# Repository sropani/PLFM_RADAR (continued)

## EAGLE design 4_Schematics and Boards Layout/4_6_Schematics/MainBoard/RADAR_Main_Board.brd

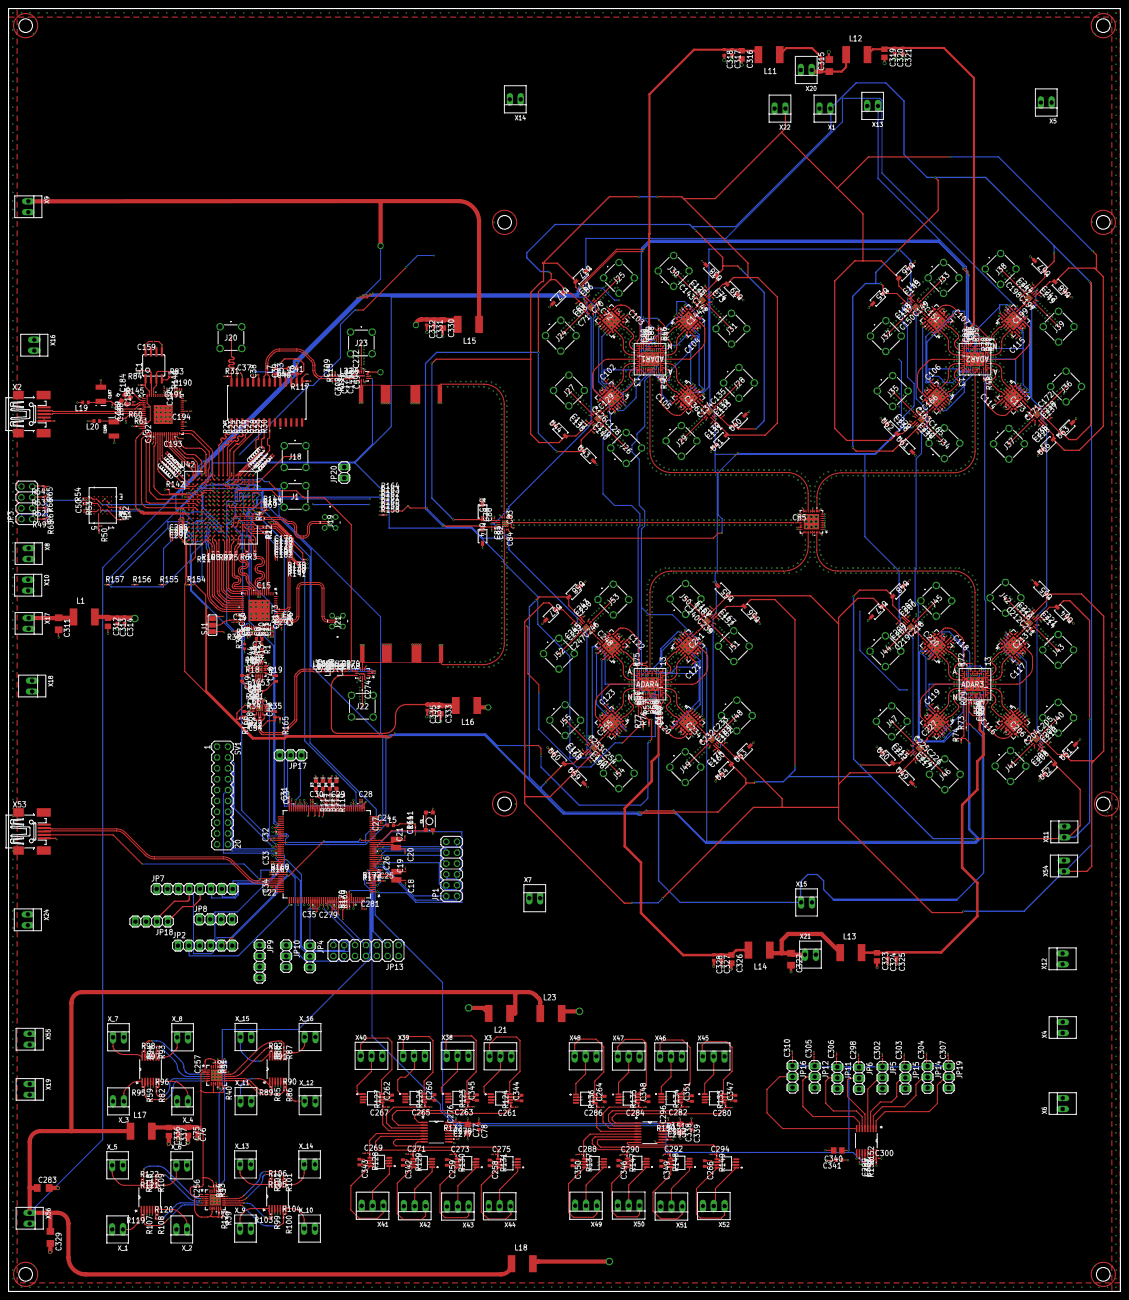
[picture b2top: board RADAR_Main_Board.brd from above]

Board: 10 copper layers, 260.0 x 300.0 mm, 789 parts (0 on the bottom side), 649 nets.

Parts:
ADAR1_, ADAR2_, ADAR3_, ADAR4_: ADAR1000ACCZN; CC-88-1_ADI
ADTR1107_1, ADTR1107_2, ADTR1107_3, ADTR1107_4, ADTR1107_5, ADTR1107_6, ADTR1107_7, ADTR1107_8, ADTR1107_9, ADTR1107_10, ADTR1107_11, ADTR1107_12, ADTR1107_13, ADTR1107_14, ADTR1107_15, ADTR1107_16: ADTR1107ACCZ; CC-24-8_ADI
C1, C2, C4, C5, C6, C7, C8, C9, C10, C11, C12, C13, C14, C15, C16, C36, C38, C39, C41, C42, C44, C45, C46, C47, C51, C52, C53, C56, C67, C69, C74, C80, C82, C125, C131, C133, C138, C140, C146, C148, C159, C160, C162, C168, C170, C175, C188, C189, C190, C192, C193, C194, C195, C196, C201, C203, C208, C210, C215, C217, C222, C224, C229, C231, C236, C238, C243, C245, C250, C252, C293: 0.1uF; C0201
C3: 2.7pF; C0402
C17, C55, C176, C285: 47uF; C0201
C18, C19: 2.7pF; C0201
C20, C21: 4.3pF; C0201
C22, C23, C164: 2.2uF; C0201
C24, C25, C26, C27, C28, C29, C30, C32, C33, C34, C35, C50, C256, C257, C279, C281, C298, C302, C303, C304, C305, C306, C307, C310: 100nF; C0201
C31: 47nF; C0201
C37, C40: 10uF; C0201
C43: 0.2pF; C0201
C48, C49, C57, C58: 0.1µF; C0402
C54: 0.6pF; C0201
C59, C127: 32.8pF; C0201
C60, C63: 103pF; C0201
C61, C62: 7.8pF; C0201
C64, C65, C268, C270: 25pF; C0201
C66, C68, C73, C79, C81, C124, C130, C132, C137, C139, C145, C147, C152, C161, C167, C169, C174, C183, C200, C202, C207, C209, C214, C216, C221, C223, C228, C230, C235, C237, C242, C244, C249, C251: 100pF; C0201
C70, C71, C72, C83, C84, C85, C126, C128, C129, C134, C135, C136, C142, C143, C144, C149, C150, C151, C163, C165, C166, C171, C172, C173, C197, C198, C199, C204, C205, C206, C211, C212, C213, C218, C219, C220, C225, C226, C227, C232, C233, C234, C239, C240, C241, C246, C247, C248, C253, C254, C255: 1pF; C0201
C75, C77, C312, C316, C319, C323, C326, C330, C333, C336, C338, C340: 10µF; C0805
C76, C78, C258, C259, C260, C262, C264, C266, C313, C317, C320, C324, C327, C331, C334, C337, C339, C341, C342, C343, C344, C345, C346, C347, C348, C349, C350, C351: 100nF; C0402
C86, C87, C88, C89, C90, C91, C92, C93, C94, C95, C96, C97, C98, C99, C100, C101: 1uF; C0201
C102, C103, C104, C105, C106, C107, C114, C115, C116, C117, C118, C119, C120, C121, C122, C123: 10nF; C0201
C108, C109, C153, C154, C177, C178, C287, C289: 4.7uF; C0201
C110, C111, C112, C113, C155, C156, C157, C158, C179, C180, C181, C182, C291: 0.47uF; C0201
C141: 106pF; C0201
C184, C185: 12pF; C0201
C186, C187: 4.7uF 35V; EIA3528
C191: 3.3uF; C0201
C261, C263, C265, C267, C269, C271, C273, C275, C280, C282, C284, C286, C288, C290, C292, C294: 4.7nF; C0201
C272, C274: 18pF; C0201
C276, C296, C300: 1µF; C0201
C277, C278, C295, C297, C299, C301: 0.1µF; C0201
C283, C311, C315, C322, C329: 22µF; C1206
C308, C309: 22pF; C0201
C314, C318, C321, C325, C328, C332, C335: 1nF; C0402
D2, D3, D4, D5: Blue; LED-0603
IC1: AT93C46A-10SQ-2.7; SOIC8
J1, J18, J20, J22, J23, J24, J25, J26, J27, J28, J29, J30, J31, J32, J33, J34, J35, J36, J37, J38, J39, J40, J41, J42, J43, J44, J45, J46, J47, J48, J49, J50, J51, J52, J53, J54, J55: 142-0731-211; 1420731211
J19, J21: CJT-T-P-HH-ST-TH1; CJTTPHHSTTH1
JP1: 2X06
JP2: 1X06
JP3: 2X04
JP4, JP5, JP6, JP10, JP11, JP12, JP14, JP15, JP16, JP17, JP19: 1X03
JP7: 1X08
JP8, JP9, JP18: 1X04
JP13: 2X07
JP20: 1X02
L1, L11, L12, L13, L14, L15, L16, L17, L18, L21, L23: L5650M
L2, L8: 12nH; L0201
L3, L4: 159nH; L0201
L5, L6, L7, L19, L20: BLM15HB121SN1; 0402
L9, L10, L24, L28: 50nH; L0201
L22, L25, L26, L27: 107.3nH; L0201
OPA_1, OPA_2, OPA_3, OPA_4: OPA4703EA/250; PW14
R1, R13: 24R; R0402
R2, R3, R4, R5, R6, R7, R8, R9, R10, R11, R12, R173: 100R; R0201
R14: 115R; R0201
R15, R32: 4.3k; R0201
R16, R17, R20, R21: 200R; R0201
R18, R19, R34, R35: 0R; R0201
R22: 56R; R0201
R23, R24, R25, R26, R27, R28, R29, R30, R49, R51, R62, R63, R64: 22R; R0201
R31, R115, R116: 50R; R0201
R33: 3k2; R0201
R36: 830R; R0402
R37: 1k; R0402
R38: 20k; R0402
R39, R40, R83, R84, R111, R123, R145, R151, R153: 10k; R0201
R41, R43, R55, R56, R57, R58, R59, R61, R82, R85, R86, R87, R88, R93, R94, R99, R100, R101, R102, R107, R108, R109, R118, R124, R125, R126, R127, R128, R129, R130, R131, R133, R134, R135, R136, R137, R138, R139, R140, R144, R147, R148, R149, R167, R168, R169, R170, R171, R172: 1k; R0201
R42, R44, R45, R46, R47, R48, R50, R52, R53, R54, R65, R66, R67, R68, R69, R70, R71, R72, R73, R74, R75, R76, R77, R117, R141, R142, R143: 4.7k; R0201
R60: 1k2_1%; R0201
R78, R79, R80, R81: 840R; R0201
R89, R90, R91, R92, R95, R96, R97, R98, R103, R104, R105, R106, R119, R120, R121, R122: 2.443k; R0201
R110, R112, R113, R114: 500R; R0201
R132, R150, R152: 5R; R0201
R146: 2.2k; R0201
R154, R155, R156, R157, R158, R159, R160, R161, R162, R163, R164: 22.1k; R0201
R165, R166: 25R; R0201
RF_SW_1, RF_SW_2, RF_SW_3, RF_SW_4, RF_SW_5, RF_SW_6, RF_SW_7, RF_SW_8, RF_SW_9, RF_SW_10, RF_SW_11, RF_SW_12, RF_SW_13, RF_SW_14, RF_SW_15, RF_SW_16: M3SWA2-34DR+; 16_QFN
S1: MOMENTARY-SWITCH-SPST-SMD-4.6X2.8MM; TACTILE_SWITCH_SMD_4.6X2.8MM
SJ1: SJ_2
SV1: MA10-2
U1: AD9484BCPZ-500; CP_56_5_ADI
U2: STM32F746ZGT7; LQFP-144_STM
U3: AD9708AR; RW_28_ADI
U4, U8: AD8352ACPZ-R7; CP_16_3_ADI
U5, U13: LTC5552IUDBTRMPBF; UDB_12_ADI
U6: FT2232HQ; 64QFN_FT2232HQ_FTD
U7, U69: DAC5578SRGET; RGE24_2P7X2P7
U9: MT25QL01GBBB8E12-0AUT; BGA24_MT25QL_MRN
U10, U88, U89: ADS7830IPWR; PW16
U11, U73, U74, U75, U76, U77, U78, U79, U80, U81, U82, U83, U84, U85, U86, U87: INA241A3IDGKRDGK0008A-MFG; DGK0008A-MFG
U14, U15, U17, U37, U38, U39, U40, U41, U43, U44, U45, U46, U47, U48, U49, U50, U51, U52, U53, U54, U55, U56, U57, U58, U59, U60, U61, U62, U63, U64, U65, U66, U67, U68: SZMMSZ5232BT1G; SOD-123_ONS
U16: EP4RKU+; DG1677-2_MNC
U42: XC7A50T-2FTG256I; BGA256C100P16X16_1700X1700X155
U$1: M3SWA2-34DR+; 16_QFN
U$2, U$3: BPF2
X1, X4, X5, X6, X7, X8, X9, X10, X11, X12, X13, X14, X15, X16, X17, X18, X19, X20, X21, X22, X24, X54, X55, X56: 22-23-2021
X2, X53: MINI-USB-32005-201; 32005-201
X3, X38, X39, X40, X41, X42, X43, X44, X45, X46, X47, X48, X49, X50, X51, X52: 22-23-2031
XTAL1: NX3225GD-8MHZ-STD-CRA-3; XTAL_NX3225GD-8MHZ-STD-CRA-3_N
XTAL3: NX3215SA-32.768KHz; XTAL_NX3225GD-8MHZ-STD-CRA-3_N
X_1, X_2, X_3, X_4, X_5, X_6, X_7, X_8, X_9, X_10, X_11, X_12, X_13, X_14, X_15, X_16: 22-23-2021
Y1: ECS-120-10-36B2-JTN-TR; CRYSTAL-SMD-2X2.5MM

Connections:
+1V0_FPGA: U42.E10, U42.F7, U42.F9, U42.F11, U42.G6, U42.H9, U42.J6, U42.J8, U42.K9, U42.L8, X8.1
+1V8_CLOCK: C311.1, L1.1, X17.1
+1V8_CLOCK_F: C4.2, C5.2, C6.2, C7.2, C8.2, C9.2, C10.2, C11.2, C12.2, C13.2, C14.2, C293.2, C312.1, C313.1, C314.1, L1.2, SJ1.3, U1.27, U1.30, U1.32, U1.33, U1.34, U1.37, U1.38, U1.39, U1.41, U1.42, U1.43, U1.46
+1V8_FPGA: C15.2, C16.2, C36.2, C285.2, C287.2, C289.2, C291.2, R154.1, R155.1, R156.1, R157.1, U1.7, U1.24, U1.47, U42.F8, U42.G8, U42.G10, U42.J10, U42.K11, U42.L10, U42.M3, U42.R4, U42.T1, X10.1
+3V3: C25.1, C26.1, C27.1, C28.1, C29.1, C30.1, C31.1, C32.1, C33.1, C34.1, C35.1, C279.1, C281.1, JP2.1, JP7.2, JP8.1, JP18.4, L5.2, R111.2, R167.1, R168.1, R169.1, R170.1, R171.1, R172.1, U2.6, U2.17, U2.30, U2.39, U2.52, U2.62, U2.72, U2.84, U2.95, U2.108, U2.121, U2.131, U2.143, U2.144, X24.1
+3V3_ADAR1_F: ADAR1_.M10, ADAR1_.M11, ADAR1_.N11, C316.1, C317.1, C318.1, L11.2
+3V3_ADAR2_F: ADAR2_.M10, ADAR2_.M11, ADAR2_.N11, C319.1, C320.1, C321.1, L12.2, R78.1
+3V3_ADAR3_F: ADAR3_.M10, ADAR3_.M11, ADAR3_.N11, C323.1, C324.1, C325.1, L13.2, R79.1
+3V3_ADAR4_F: ADAR4_.M10, ADAR4_.M11, ADAR4_.N11, C326.1, C327.1, C328.1, L14.2, R80.1, R81.1
+3V3_ADAR12: C315.1, L11.1, L12.1, X20.1
+3V3_ADAR34: C322.1, L13.1, L14.1, X21.1
+3V3_ADTR: ADTR1107_1.24, ADTR1107_2.24, ADTR1107_3.24, ADTR1107_4.24, ADTR1107_5.24, ADTR1107_6.24, ADTR1107_7.24, ADTR1107_8.24, ADTR1107_9.24, ADTR1107_10.24, ADTR1107_11.24, ADTR1107_12.24, ADTR1107_13.24, ADTR1107_14.24, ADTR1107_15.24, ADTR1107_16.24, X4.1
+3V3_AN: C40.1, C42.1, C283.1, C329.1, L6.2, L15.1, L16.1, L17.1, L18.1, L21.1, L23.1, X9.1, X56.1
+3V3_AN1_F: C330.1, C331.1, C332.1, L15.2, U5.9
+3V3_AN2_F: C333.1, C334.1, C335.1, L16.2, U13.9
+3V3_AN3_F: C75.1, C76.1, C256.1, C257.1, C336.1, C337.1, L17.2, R39.2, R40.2, R42.1, R44.1, R123.2, U7.2, U7.8, U7.9, U69.2, U69.8, U69.9
+3V3_AN4_F: C77.1, C78.1, C298.1, C302.1, C303.1, C304.1, C305.1, C306.1, C307.1, C310.1, C338.1, C339.1, C340.1, C341.1, JP5.1, JP6.1, JP11.1, JP12.1, JP14.1, JP15.1, JP16.1, JP19.1, L18.2, R132.1, R150.1, R152.1
+3V3_AN5_F: C258.1, C259.1, C260.1, C262.1, C342.1, C343.1, C344.1, C345.1, L21.2, U11.6, U73.6, U74.6, U75.6, U76.6, U77.6, U78.6, U79.6
+3V3_AN6_F: C264.1, C266.1, C346.1, C347.1, C348.1, C349.1, C350.1, C351.1, L23.2, U80.6, U81.6, U82.6, U83.6, U84.6, U85.6, U86.6, U87.6
+3V3_FPGA: C17.2, C37.1, C41.1, C50.2, C55.2, C108.2, C109.2, C110.2, C111.2, C112.2, C113.2, C153.2, C154.2, C155.2, C156.2, C157.2, C158.2, C159.2, C176.2, C177.2, C178.2, C179.2, C180.2, C181.2, C182.2, C190.2, C192.2, C193.2, C194.2, C195.2, IC1.8, JP3.2, L19.2, L20.2, R50.2, R52.2, R53.2, R54.1, R61.1, R65.2, R66.2, R67.2, R68.2, R69.2, R83.2, R84.2, R138.1, R141.1, R142.1, R143.2, R144.2, R145.2, U3.17, U3.27, U6.20, U6.31, U6.42, U6.50, U6.56, U9.B4, U42.A6, U42.A16, U42.B3, U42.B13, U42.C10, U42.D7, U42.E4, U42.E14, U42.F1, U42.H15, U42.J2, U42.J12, U42.L6, U42.L16, U42.M13, U42.N10, U42.P7, U42.R14, U42.T11, X16.1
+3V3_VDD_SW: ADTR1107_1.19, ADTR1107_2.19, ADTR1107_3.19, ADTR1107_4.19, ADTR1107_5.19, ADTR1107_6.19, ADTR1107_7.19, ADTR1107_8.19, ADTR1107_9.19, ADTR1107_10.19, ADTR1107_11.19, ADTR1107_12.19, ADTR1107_13.19, ADTR1107_14.19, ADTR1107_15.19, ADTR1107_16.19, X12.1
+3V4: C68.1, C69.1, C81.1, C82.1, C124.1, C125.1, C132.1, C133.1, C139.1, C140.1, C147.1, C148.1, C161.1, C162.1, C169.1, C170.1, C183.1, C196.1, C202.1, C203.1, C209.1, C210.1, C216.1, C217.1, C223.1, C224.1, C230.1, C231.1, C237.1, C238.1, C244.1, C245.1, C251.1, C252.1, RF_SW_1.8, RF_SW_2.8, RF_SW_3.8, RF_SW_4.8, RF_SW_5.8, RF_SW_6.8, RF_SW_7.8, RF_SW_8.8, RF_SW_9.8, RF_SW_10.8, RF_SW_11.8, RF_SW_12.8, RF_SW_13.8, RF_SW_14.8, RF_SW_15.8, RF_SW_16.8, U14.1, U17.1, U38.1, U40.1, U43.1, U45.1, U47.1, U49.1, U51.1, U53.1, U55.1, U57.1, U59.1, U61.1, U63.1, U65.1, U67.1, U$1.8, X1.1, X54.1
+5V0_0: U4.8, U4.13, U8.8, U8.13, X18.1
+5V0_PA_1: ADTR1107_1.8, ADTR1107_2.8, ADTR1107_3.8, ADTR1107_4.8, ADTR1107_7.8, X14.1
+5V0_PA_2: ADTR1107_5.8, ADTR1107_6.8, ADTR1107_8.8, ADTR1107_10.8, ADTR1107_12.8, X5.1
+5V0_PA_3: ADTR1107_9.8, ADTR1107_11.8, ADTR1107_13.8, ADTR1107_14.8, ADTR1107_15.8, ADTR1107_16.8, X7.1
+5V5_PA: OPA_1.4, OPA_2.4, OPA_3.4, OPA_4.4, X55.1
-3V3_SW: ADTR1107_1.21, ADTR1107_2.21, ADTR1107_3.21, ADTR1107_4.21, ADTR1107_5.21, ADTR1107_6.21, ADTR1107_7.21, ADTR1107_8.21, ADTR1107_9.21, ADTR1107_10.21, ADTR1107_11.21, ADTR1107_12.21, ADTR1107_13.21, ADTR1107_14.21, ADTR1107_15.21, ADTR1107_16.21, X6.1
-3V4: C66.1, C67.1, C73.1, C74.1, C79.1, C80.1, C130.1, C131.1, C137.1, C138.1, C145.1, C146.1, C152.1, C160.1, C167.1, C168.1, C174.1, C175.1, C200.1, C201.1, C207.1, C208.1, C214.1, C215.1, C221.1, C222.1, C228.1, C229.1, C235.1, C236.1, C242.1, C243.1, C249.1, C250.1, RF_SW_1.5, RF_SW_2.5, RF_SW_3.5, RF_SW_4.5, RF_SW_5.5, RF_SW_6.5, RF_SW_7.5, RF_SW_8.5, RF_SW_9.5, RF_SW_10.5, RF_SW_11.5, RF_SW_12.5, RF_SW_13.5, RF_SW_14.5, RF_SW_15.5, RF_SW_16.5, U15.2, U37.2, U39.2, U41.2, U44.2, U46.2, U48.2, U50.2, U52.2, U54.2, U56.2, U58.2, U60.2, U62.2, U64.2, U66.2, U68.2, U$1.5, X11.1, X22.1
-5V0_ADAR12: ADAR1_.B11, ADAR2_.B11, X13.1
-5V0_ADAR34: ADAR3_.B11, ADAR4_.B11, X15.1
-5V5_PA: OPA_1.11, OPA_2.11, OPA_3.11, OPA_4.11, X19.1
ACC_INT: JP7.7, U2.97
AD9523_CS: JP1.5, U2.19
AD9523_EEPROM_SEL: JP1.11, U2.22
AD9523_PD: JP1.1, U2.13
AD9523_REF_SEL: JP1.2, U2.14
AD9523_RESET: JP1.4, U2.18
AD9523_STATUS0: JP1.9, U2.20
AD9523_STATUS1: JP1.10, U2.21
AD9523_SYNC: JP1.3, U2.15
ADAR_1_CS_1V8: ADAR1_.M3, R154.2, U42.L5
ADAR_1_CS_3V3: U2.34, U42.F14
ADAR_2_CS_1V8: ADAR2_.M3, R155.2, U42.L4
ADAR_2_CS_3V3: U2.35, U42.H16
ADAR_3_CS_1V8: ADAR3_.M3, R156.2, U42.M4
ADAR_3_CS_3V3: U2.36, U42.G16
ADAR_4_CS_1V8: ADAR4_.M3, R157.2, U42.M2
ADAR_4_CS_3V3: U2.37, U42.J15
ADAR_RX_LOAD_1: ADAR1_.N2, R47.2, U42.M5
ADAR_RX_LOAD_2: ADAR2_.N2, R71.2, U42.T2
ADAR_RX_LOAD_3: ADAR3_.N2, R74.2, U42.R1
ADAR_RX_LOAD_4: ADAR4_.N2, R77.2, U42.N4
ADAR_TR_1: ADAR1_.N6, R158.2, U42.N2
ADAR_TR_2: ADAR2_.N6, R159.2, U42.N1
ADAR_TR_3: ADAR3_.N6, R160.2, U42.P1
ADAR_TR_4: ADAR4_.N6, R161.2, U42.P4
ADAR_TX_LOAD_1: ADAR1_.N3, R46.2, U42.P3
ADAR_TX_LOAD_2: ADAR2_.N3, R70.2, U42.T4
ADAR_TX_LOAD_3: ADAR3_.N3, R73.2, U42.R3
ADAR_TX_LOAD_4: ADAR4_.N3, R76.2, U42.R2
ADC_CLK_IN_N: C2.1, R173.2, U1.45
ADC_CLK_IN_P: C1.1, R173.1, U1.44
ADC_D0_N: R2.1, U1.3, U42.P16
ADC_D0_P: R2.2, U1.4, U42.P15
ADC_D1_N: R3.1, U1.5, U42.R16
ADC_D1_P: R3.2, U1.6, U42.R15
ADC_D2_N: R6.1, U1.9, U42.T15
ADC_D2_P: R6.2, U1.10, U42.T14
ADC_D3_N: R5.1, U1.11, U42.T13
ADC_D3_P: R5.2, U1.12, U42.R13
ADC_D4_N: R7.1, U1.13, U42.R11
ADC_D4_P: R7.2, U1.14, U42.R10
ADC_D5_N: R9.1, U1.15, U42.T10
ADC_D5_P: R9.2, U1.16, U42.T9
ADC_D6_N: R8.1, U1.17, U42.T8
ADC_D6_P: R8.2, U1.18, U42.T7
ADC_D7_N: R10.1, U1.19, U42.R7
ADC_D7_P: R10.2, U1.20, U42.R6
ADC_DCO_N: R12.1, U1.49, U42.P14
ADC_DCO_P: R12.2, U1.50, U42.N14
ADC_IF_IN_N: C45.2, R1.2, R17.1
ADC_IF_IN_P: C44.2, R13.2, R16.2
ADC_OR_N: R11.1, U1.21, U42.N6
ADC_OR_P: R11.2, U1.22, U42.M6
ADC_PWRD: R36.2, U42.T5
ADF4382_RX_CE: JP13.10, U2.124
ADF4382_RX_CS: JP13.9, U2.125
ADF4382_RX_DELADJ: JP13.12, U2.92
ADF4382_RX_DELSTR: JP13.11, U2.93
ADF4382_RX_LKDET: JP13.13, U2.91
ADF4382_TX_CE: JP13.5, U2.132
ADF4382_TX_CS: JP13.4, U2.129
ADF4382_TX_DELADJ: JP13.7, U2.128
ADF4382_TX_DELSTR: JP13.6, U2.127
ADF4382_TX_LKDET: JP13.8, U2.126
AMP_IF_IN_N: C48.1, C52.2, R21.1
AMP_IF_IN_P: C49.2, C51.2, R20.2
AMP_IN_N: C57.1, L10.1, R165.1
AMP_IN_P: C58.2, L9.1, R166.1
ANT1_1: ADTR1107_3.17, C72.2
ANT1_2: ADTR1107_7.17, C151.2
ANT1_3: ADTR1107_10.17, C206.2
ANT1_4: ADTR1107_14.17, C234.2
ANT2_1: ADTR1107_1.17, C129.2
ANT2_2: ADTR1107_5.17, C166.2
ANT2_3: ADTR1107_12.17, C213.2
ANT2_4: ADTR1107_16.17, C241.2
ANT3_1: ADTR1107_2.17, C136.2
ANT3_2: ADTR1107_6.17, C173.2
ANT3_3: ADTR1107_11.17, C220.2
ANT3_4: ADTR1107_15.17, C248.2
ANT4_1: ADTR1107_4.17, C144.2
ANT4_2: ADTR1107_8.17, C199.2
ANT4_3: ADTR1107_9.17, C227.2
ANT4_4: ADTR1107_13.17, C255.2
DAC_0: R30.1, U42.A14
DAC_1: R29.1, U42.A13
DAC_1_VG_CLR: R40.1, U2.134, U7.12
DAC_1_VG_LDAC: R42.2, U2.135, U7.22
DAC_2: R28.1, U42.A12
DAC_2_VG_CLR: R39.1, U2.139, U69.12
DAC_2_VG_LDAC: R44.2, U2.140, U69.22
DAC_3: R27.1, U42.B11
DAC_4: R26.1, U42.B10
DAC_5: R25.1, U42.A10
DAC_6: R24.1, U42.A9
DAC_7: R23.1, U42.A8
DAC_ACOM: L7.1, U3.20
DAC_AVDD: C39.2, L6.1, U3.16, U3.24
DAC_CLOCK: J20.1, R31.2, U3.28
DAC_IOUT_F_N: C59.2, L27.2, U5.3
DAC_IOUT_F_P: C59.1, L26.2, U5.2
DAC_IOUT_N: C127.2, C308.1, L25.1, R115.2, U3.21
DAC_IOUT_P: C127.1, C309.1, L22.1, R116.2, U3.22
DAC_SLEEP: R117.2, U3.15, U42.A15
DAC_VOUT_VG_1: R94.1, U7.3
DAC_VOUT_VG_2: R87.1, U7.16
DAC_VOUT_VG_3: R93.1, U7.4
DAC_VOUT_VG_4: R88.1, U7.15
DAC_VOUT_VG_5: R82.2, U7.5
DAC_VOUT_VG_6: R85.2, U7.14
DAC_VOUT_VG_7: R59.2, U7.6
DAC_VOUT_VG_8: R86.2, U7.13
DAC_VOUT_VG_9: R118.1, U69.3
DAC_VOUT_VG_10: R101.1, U69.16
DAC_VOUT_VG_11: R109.1, U69.4
DAC_VOUT_VG_12: R102.1, U69.15
DAC_VOUT_VG_13: R108.2, U69.5
DAC_VOUT_VG_14: R99.2, U69.14
DAC_VOUT_VG_15: R107.2, U69.6
DAC_VOUT_VG_16: R100.2, U69.13
DET1_1: ADAR1_.N13, ADTR1107_3.12
DET1_2: ADAR2_.N13, ADTR1107_7.12
DET1_3: ADAR3_.N13, ADTR1107_10.12
DET1_4: ADAR4_.N13, ADTR1107_14.12
DET2_1: ADAR1_.G13, ADTR1107_1.12
DET2_2: ADAR2_.G13, ADTR1107_5.12
DET2_3: ADAR3_.G13, ADTR1107_12.12
DET2_4: ADAR4_.G13, ADTR1107_16.12
DET3_1: ADAR1_.A1, ADTR1107_2.12
DET3_2: ADAR2_.A1, ADTR1107_6.12
DET3_3: ADAR3_.A1, ADTR1107_11.12
DET3_4: ADAR4_.A1, ADTR1107_15.12
DET4_1: ADAR1_.G1, ADTR1107_4.12
DET4_2: ADAR2_.G1, ADTR1107_8.12
DET4_3: ADAR3_.G1, ADTR1107_9.12
DET4_4: ADAR4_.G1, ADTR1107_13.12
DIG_0: U2.77, U42.F13
DIG_1: U2.78, U42.E16
DIG_2: U2.79, U42.D16
DIG_3: U2.80, U42.F15
DIG_4: U2.81, U42.E15
DIG_5: U2.82, U42.H11
DIG_6: U2.85, U42.G12
DIG_7: U2.86, U42.H12
EN/DIS_COOLING: JP4.1, U2.123
EN/DIS_RFPA_VDD: JP10.1, U2.122
EN_+1V0_FPGA: SV1.1, U2.58
EN_+1V8_CLOCK: SV1.8, U2.89
EN_+1V8_FPGA: SV1.3, U2.59
EN_+3V3_ADAR12: SV1.9, U2.64
EN_+3V3_ADAR34: SV1.11, U2.65
EN_+3V3_ADTR: SV1.13, U2.66
EN_+3V3_CLOCK: SV1.10, U2.90
EN_+3V3_FPGA: SV1.5, U2.60
EN_+3V3_SW: SV1.15, U2.67
EN_+3V3_VDD_SW: SV1.17, U2.68
EN_+5V0_ADAR: SV1.7, U2.63
EN_+5V0_PA1: SV1.19, U2.56
EN_+5V0_PA2: SV1.2, U2.57
EN_+5V0_PA3: SV1.4, U2.87
EN_+5V5_PA: SV1.6, U2.88
FPGA_ADC_CLOCK_N: J19.2, R4.1, U42.N12
FPGA_ADC_CLOCK_P: J19.1, R4.2, U42.N11
FPGA_CLOCK_TEST: JP20.1, U42.H14
FPGA_DAC_CLOCK: J18.1, U42.C13
FPGA_FLASH_CLK: R51.2, U42.E8
FPGA_FLASH_DQ0: U9.D3, U42.J13
FPGA_FLASH_DQ1: U9.D2, U42.J14
FPGA_FLASH_DQ2: R53.1, U9.C4, U42.K15
FPGA_FLASH_DQ3: R54.2, U9.D4, U42.K16
FPGA_FLASH_NCS: R52.1, U9.C2, U42.L12
FPGA_FLASH_NRST: R50.1, U9.A4, U42.L13
FPGA_PUDC_B: R69.1, U42.L15
FPGA_SYS_CLOCK: J1.1, U42.E12
FPGA_TCK: R62.1, R67.1, U42.L7
FPGA_TDI: R64.1, R65.1, U42.N7
FPGA_TDO: R63.1, R66.1, U42.N8
FPGA_TMS: R49.1, R68.1, U42.M7
FT2232_USB_D_N: U6.7, X2.2
FT2232_USB_D_P: U6.8, X2.3
FT_+1V8: C191.2, U6.12, U6.37, U6.49, U6.64
FT_CLKOUT: U6.32, U42.C4
FT_D0: U6.16, U42.K1
FT_D1: U6.17, U42.J3
FT_D2: U6.18, U42.H3
FT_D3: U6.19, U42.G4
FT_D4: U6.21, U42.F2
FT_D5: U6.22, U42.D1
FT_D6: U6.23, U42.C3
FT_D7: U6.24, U42.C1
FT_OE#: U6.33, U42.B7
FT_RD#: U6.28, U42.A3
FT_RESET#: R61.2, U6.14
FT_RXF#: U6.26, U42.A2
FT_SIWUA: U6.30, U42.A5
FT_TXE#: U6.27, U42.B2
FT_WR#: U6.29, U42.A4
GND: ADAR1_.89, ADAR1_.A2, ADAR1_.A6, ADAR1_.A8, ADAR1_.A12, ADAR1_.A13, ADAR1_.B1, ADAR1_.B2, ADAR1_.B6, ADAR1_.B7, ADAR1_.B8, ADAR1_.B9, ADAR1_.B10, ADAR1_.B12, ADAR1_.B13, ADAR1_.C2, ADAR1_.C12, ADAR1_.D1, ADAR1_.D2, ADAR1_.D12, ADAR1_.D13, ADAR1_.E2, ADAR1_.E12, ADAR1_.F1, ADAR1_.F2, ADAR1_.F12, ADAR1_.F13, ADAR1_.G2, ADAR1_.G12, ADAR1_.H1, ADAR1_.H2, ADAR1_.H12, ADAR1_.H13, ADAR1_.J2, ADAR1_.J12, ADAR1_.K1, ADAR1_.K2, ADAR1_.K12, ADAR1_.K13, ADAR1_.L2, ADAR1_.L12, ADAR1_.M1, ADAR1_.M2, ADAR1_.M7, ADAR1_.M12, ADAR1_.M13, ADAR1_.N1, ADAR1_.N4, ADAR1_.N5, ADAR1_.N7, ADAR1_.N8, ADAR1_.N12, ADAR2_.89, ADAR2_.A2, ADAR2_.A6, ADAR2_.A8, ADAR2_.A12, ADAR2_.A13, ADAR2_.B1, ADAR2_.B2, ADAR2_.B6, ADAR2_.B7, ADAR2_.B8, ADAR2_.B9, ADAR2_.B10, ADAR2_.B12, ADAR2_.B13, ADAR2_.C2, ADAR2_.C12, ADAR2_.D1, ADAR2_.D2, ADAR2_.D12, ADAR2_.D13, ADAR2_.E2, ADAR2_.E12, ADAR2_.F1, ADAR2_.F2, ADAR2_.F12, ADAR2_.F13, ADAR2_.G2, ADAR2_.G12, ADAR2_.H1, ADAR2_.H2, ADAR2_.H12, ADAR2_.H13, ADAR2_.J2, ADAR2_.J12, ADAR2_.K1, ADAR2_.K2, ADAR2_.K12, ADAR2_.K13, ADAR2_.L2, ADAR2_.L12, ADAR2_.M1, ADAR2_.M2, ADAR2_.M7, ADAR2_.M12, ADAR2_.M13, ADAR2_.N1, ADAR2_.N4, ADAR2_.N7, ADAR2_.N8, ADAR2_.N12, ADAR3_.89, ADAR3_.A2, ADAR3_.A6, ADAR3_.A8, ADAR3_.A12, ADAR3_.A13, ADAR3_.B1, ADAR3_.B2, ADAR3_.B6, ADAR3_.B7, ADAR3_.B8, ADAR3_.B9, ADAR3_.B10, ADAR3_.B12, ADAR3_.B13, ADAR3_.C2, ADAR3_.C12, ADAR3_.D1, ADAR3_.D2, ADAR3_.D12, ADAR3_.D13, ADAR3_.E2, ADAR3_.E12, ADAR3_.F1, ADAR3_.F2, ADAR3_.F12, ADAR3_.F13, ADAR3_.G2, ADAR3_.G12, ADAR3_.H1, ADAR3_.H2, ADAR3_.H12, ADAR3_.H13, ADAR3_.J2, ADAR3_.J12, ADAR3_.K1, ADAR3_.K2, ADAR3_.K12, ADAR3_.K13, ADAR3_.L2, ADAR3_.L12, ADAR3_.M1, ADAR3_.M2, ADAR3_.M7, ADAR3_.M12, ADAR3_.M13, ADAR3_.N1, ADAR3_.N5, ADAR3_.N7, ADAR3_.N8, ADAR3_.N12, ADAR4_.89, ADAR4_.A2, ADAR4_.A6, ADAR4_.A8, ADAR4_.A12, ADAR4_.A13, ADAR4_.B1, ADAR4_.B2, ADAR4_.B6, ADAR4_.B7, ADAR4_.B8, ADAR4_.B9, ADAR4_.B10, ADAR4_.B12, ADAR4_.B13, ADAR4_.C2, ADAR4_.C12, ADAR4_.D1, ADAR4_.D2, ADAR4_.D12, ADAR4_.D13, ADAR4_.E2, ADAR4_.E12, ADAR4_.F1, ADAR4_.F2, ADAR4_.F12, ADAR4_.F13, ADAR4_.G2, ADAR4_.G12, ADAR4_.H1, ADAR4_.H2, ADAR4_.H12, ADAR4_.H13, ADAR4_.J2, ADAR4_.J12, ADAR4_.K1, ADAR4_.K2, ADAR4_.K12, ADAR4_.K13, ADAR4_.L2, ADAR4_.L12, ADAR4_.M1, ADAR4_.M2, ADAR4_.M7, ADAR4_.M12, ADAR4_.M13, ADAR4_.N1, ADAR4_.N7, ADAR4_.N8, ADAR4_.N12, ADTR1107_1.1, ADTR1107_1.3, ADTR1107_1.4, ADTR1107_1.6, ADTR1107_1.9, ADTR1107_1.10, ADTR1107_1.11, ADTR1107_1.13, ADTR1107_1.14, ADTR1107_1.15, ADTR1107_1.16, ADTR1107_1.18, ADTR1107_1.22, ADTR1107_1.25, ADTR1107_2.1, ADTR1107_2.3, ADTR1107_2.4, ADTR1107_2.6, ADTR1107_2.9, ADTR1107_2.10, ADTR1107_2.11, ADTR1107_2.13, ADTR1107_2.14, ADTR1107_2.15, ADTR1107_2.16, ADTR1107_2.18, ADTR1107_2.22, ADTR1107_2.25, ADTR1107_3.1, ADTR1107_3.3, ADTR1107_3.4, ADTR1107_3.6, ADTR1107_3.9, ADTR1107_3.10, ADTR1107_3.11, ADTR1107_3.13, ADTR1107_3.14, ADTR1107_3.15, ADTR1107_3.16, ADTR1107_3.18, ADTR1107_3.22, ADTR1107_3.25, ADTR1107_4.1, ADTR1107_4.3, ADTR1107_4.4, ADTR1107_4.6, ADTR1107_4.9, ADTR1107_4.10, ADTR1107_4.11, ADTR1107_4.13, ADTR1107_4.14, ADTR1107_4.15, ADTR1107_4.16, ADTR1107_4.18, ADTR1107_4.22, ADTR1107_4.25, ADTR1107_5.1, ADTR1107_5.3, ADTR1107_5.4, ADTR1107_5.6, ADTR1107_5.9, ADTR1107_5.10, ADTR1107_5.11, ADTR1107_5.13, ADTR1107_5.14, ADTR1107_5.15, ADTR1107_5.16, ADTR1107_5.18, ADTR1107_5.22, ADTR1107_5.25, ADTR1107_6.1, ADTR1107_6.3, ADTR1107_6.4, ADTR1107_6.6, ADTR1107_6.9, ADTR1107_6.10, ADTR1107_6.11, ADTR1107_6.13, ADTR1107_6.14, ADTR1107_6.15, ADTR1107_6.16, ADTR1107_6.18, ADTR1107_6.22, ADTR1107_6.25, ADTR1107_7.1, ADTR1107_7.3, ADTR1107_7.4, ADTR1107_7.6, ADTR1107_7.9, ADTR1107_7.10, ADTR1107_7.11, ADTR1107_7.13, ADTR1107_7.14, ADTR1107_7.15, ADTR1107_7.16, ADTR1107_7.18, ADTR1107_7.22, ADTR1107_7.25, ADTR1107_8.1, ADTR1107_8.3, ADTR1107_8.4, ADTR1107_8.6, ADTR1107_8.9, ADTR1107_8.10, ADTR1107_8.11, ADTR1107_8.13, ADTR1107_8.14, ADTR1107_8.15, ADTR1107_8.16, ADTR1107_8.18, ADTR1107_8.22, ADTR1107_8.25, ADTR1107_9.1, ADTR1107_9.3, ADTR1107_9.4, ADTR1107_9.6, ADTR1107_9.9, ADTR1107_9.10, ADTR1107_9.11, ADTR1107_9.13, ADTR1107_9.14, ADTR1107_9.15, ADTR1107_9.16, ADTR1107_9.18, ADTR1107_9.22, ADTR1107_9.25, ADTR1107_10.1, ADTR1107_10.3, ADTR1107_10.4, ADTR1107_10.6, ADTR1107_10.9, ADTR1107_10.10, ADTR1107_10.11, ADTR1107_10.13, ADTR1107_10.14, ADTR1107_10.15, ADTR1107_10.16, ADTR1107_10.18, ADTR1107_10.22, ADTR1107_10.25, ADTR1107_11.1, ADTR1107_11.3, ADTR1107_11.4, ADTR1107_11.6, ADTR1107_11.9, ADTR1107_11.10, ADTR1107_11.11, ADTR1107_11.13, ADTR1107_11.14, ADTR1107_11.15, ADTR1107_11.16, ADTR1107_11.18, ADTR1107_11.22, ADTR1107_11.25, ADTR1107_12.1, ADTR1107_12.3, ADTR1107_12.4, ADTR1107_12.6, ADTR1107_12.9, ADTR1107_12.10, ADTR1107_12.11, ADTR1107_12.13, ADTR1107_12.14, ADTR1107_12.15, ADTR1107_12.16, ADTR1107_12.18, ADTR1107_12.22, ADTR1107_12.25, ADTR1107_13.1, ADTR1107_13.3, ADTR1107_13.4, ADTR1107_13.6, ADTR1107_13.9, ADTR1107_13.10, ADTR1107_13.11, ADTR1107_13.13, ADTR1107_13.14, ADTR1107_13.15, ADTR1107_13.16, ADTR1107_13.18, ADTR1107_13.22, ADTR1107_13.25, ADTR1107_14.1, ADTR1107_14.3, ADTR1107_14.4, ADTR1107_14.6, ADTR1107_14.9, ADTR1107_14.10, ADTR1107_14.11, ADTR1107_14.13, ADTR1107_14.14, ADTR1107_14.15, ADTR1107_14.16, ADTR1107_14.18, ADTR1107_14.22, ADTR1107_14.25, ADTR1107_15.1, ADTR1107_15.3, ADTR1107_15.4, ADTR1107_15.6, ADTR1107_15.9, ADTR1107_15.10, ADTR1107_15.11, ADTR1107_15.13, ADTR1107_15.14, ADTR1107_15.15, ADTR1107_15.16, ADTR1107_15.18, ADTR1107_15.22, ADTR1107_15.25, ADTR1107_16.1, ADTR1107_16.3, ADTR1107_16.4, ADTR1107_16.6, ADTR1107_16.9, ADTR1107_16.10, ADTR1107_16.11, ADTR1107_16.13, ADTR1107_16.14, ADTR1107_16.15, ADTR1107_16.16, ADTR1107_16.18, ADTR1107_16.22, ADTR1107_16.25, C4.1, C5.1, C6.1, C7.1, C8.1, C9.1, C10.1, C11.1, C12.1, C13.1, C14.1, C15.1, C16.1, C17.1, C18.2, C19.2, C20.2, C21.2, C22.2, C23.2, C24.2, C25.2, C26.2, C27.2, C28.2, C29.2, C30.2, C31.2, C32.2, C33.2, C34.2, C35.2, C36.1, C37.2, C38.2, C40.2, C41.2, C42.2, C46.1, C47.1, C50.1, C53.1, C55.1, C56.1, C66.2, C67.2, C68.2, C69.2, C73.2, C74.2, C75.2, C76.2, C77.2, C78.2, C79.2, C80.2, C81.2, C82.2, C86.2, C87.2, C88.2, C89.2, C90.2, C91.2, C92.2, C93.2, C94.2, C95.2, C96.2, C97.2, C98.2, C99.2, C100.2, C101.2, C102.2, C103.2, C104.2, C105.2, C106.2, C107.2, C108.1, C109.1, C110.1, C111.1, C112.1, C113.1, C114.2, C115.2, C116.2, C117.2, C118.2, C119.2, C120.2, C121.2, C122.2, C123.2, C124.2, C125.2, C130.2, C131.2, C132.2, C133.2, C137.2, C138.2, C139.2, C140.2, C145.2, C146.2, C147.2, C148.2, C152.2, C153.1, C154.1, C155.1, C156.1, C157.1, C158.1, C159.1, C160.2, C161.2, C162.2, C164.1, C167.2, C168.2, C169.2, C170.2, C174.2, C175.2, C176.1, C177.1, C178.1, C179.1, C180.1, C181.1, C182.1, C183.2, C184.2, C185.2, C186.C, C187.C, C188.1, C189.2, C190.1, C191.1, C192.1, C193.1, C194.1, C195.1, C196.2, C200.2, C201.2, C202.2, C203.2, C207.2, C208.2, C209.2, C210.2, C214.2, C215.2, C216.2, C217.2, C221.2, C222.2, C223.2, C224.2, C228.2, C229.2, C230.2, C231.2, C235.2, C236.2, C237.2, C238.2, C242.2, C243.2, C244.2, C245.2, C249.2, C250.2, C251.2, C252.2, C256.2, C257.2, C258.2, C259.2, C260.2, C261.1, C262.2, C263.1, C264.2, C265.1, C266.2, C267.1, C269.1, C271.1, C273.1, C275.1, C276.2, C277.2, C278.2, C279.2, C280.1, C281.2, C282.1, C283.2, C284.1, C285.1, C286.1, C287.1, C288.1, C289.1, C290.1, C291.1, C292.1, C293.1, C294.1, C295.2, C296.2, C297.2, C298.2, C299.2, C300.2, C301.2, C302.2, C303.2, C304.2, C305.2, C306.2, C307.2, C308.2, C309.2, C310.2, C311.2, C312.2, C313.2, C314.2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
GYR_INT: JP7.8, U2.98
LNA_BIAS_1: ADAR1_.A11, ADTR1107_1.23, ADTR1107_2.23, ADTR1107_3.23, ADTR1107_4.23
LNA_BIAS_2: ADAR2_.A11, ADTR1107_5.23, ADTR1107_6.23, ADTR1107_7.23, ADTR1107_8.23
LNA_BIAS_3: ADAR3_.A11, ADTR1107_9.23, ADTR1107_10.23, ADTR1107_11.23, ADTR1107_12.23
LNA_BIAS_4: ADAR4_.A11, ADTR1107_13.23, ADTR1107_14.23, ADTR1107_15.23, ADTR1107_16.23
M3S_VCTRL: RF_SW_1.6, RF_SW_2.6, RF_SW_3.6, RF_SW_4.6, RF_SW_5.6, RF_SW_6.6, RF_SW_7.6, RF_SW_8.6, RF_SW_9.6, RF_SW_10.6, RF_SW_11.6, RF_SW_12.6, RF_SW_13.6, RF_SW_14.6, RF_SW_15.6, RF_SW_16.6, U42.G15, U$1.6
MAG_DRDY: JP7.6, U2.96
MIX_RX_EN: U13.7, U42.D11
MIX_RX_N: C270.2, U13.3
MIX_RX_P: C268.2, U13.2
MIX_TX_EN: U5.7, U42.C11
unnamed: R123.1, U69.11
unnamed: C2.2, J21.2
unnamed: C1.2, J21.1
unnamed: C3.1, R1.1, U1.36
unnamed: C43.2, R15.2, U4.1
unnamed: SJ1.2, U1.26
unnamed: C23.1, U2.71
unnamed: C22.1, U2.106
unnamed: C24.1, L5.1, U2.32, U2.33
unnamed: R23.2, U3.1
unnamed: R24.2, U3.2
unnamed: R25.2, U3.3
unnamed: R26.2, U3.4
unnamed: R27.2, U3.5
unnamed: C43.1, R15.1, U4.4
unnamed: R28.2, U3.6
unnamed: R38.2, U1.31
unnamed: R29.2, U3.7
unnamed: R30.2, U3.8
unnamed: C272.1, U5.11
unnamed: C83.2, U$1.3
unnamed: R33.1, U3.18
unnamed: C272.2, J23.1
unnamed: C274.2, J22.1
unnamed: R51.1, U9.B2
unnamed: C85.1, U$1.15
unnamed: JP3.1, R49.2
unnamed: JP3.3, R62.2
unnamed: JP3.5, R63.2
unnamed: R14.1, U4.3
unnamed: JP3.7, R64.2
unnamed: C38.1, U3.23
unnamed: C84.1, U$1.10
unnamed: ADAR1_.B3, R45.1
unnamed: ADAR2_.B3, R48.1
unnamed: R36.1, R37.2, U1.29
unnamed: ADAR2_.M9, C87.1
unnamed: C3.2, R13.1, U1.35
unnamed: ADAR2_.M8, C86.1
unnamed: ADAR2_.N10, C92.1
unnamed: R14.2, U4.2
unnamed: R19.1, U4.5
unnamed: R18.2, U4.16
unnamed: C47.2, U4.14
unnamed: R110.2, U2.50
unnamed: ADAR2_.N9, C93.1
unnamed: C44.1, U4.11
unnamed: ADAR3_.B3, R72.1
unnamed: C61.1, L3.2
unnamed: ADAR3_.M9, C95.1
unnamed: ADAR3_.M8, C94.1
unnamed: ADAR3_.N10, C96.1
unnamed: C62.1, L4.2
unnamed: ADAR3_.N9, C97.1
unnamed: ADAR4_.B3, R75.1
unnamed: C45.1, U4.10
unnamed: ADAR1_.N9, C91.1
unnamed: C46.2, R16.1, R17.2
unnamed: ADAR4_.M9, C99.1
unnamed: ADAR4_.M8, C98.1
unnamed: ADAR4_.N10, C100.1
unnamed: C64.1, L9.2
unnamed: C274.1, U13.11
unnamed: C48.2, R19.2
unnamed: C70.2, RF_SW_3.3
unnamed: ADAR4_.N9, C101.1
unnamed: ADAR1_.M9, C89.1
unnamed: ADAR1_.M8, C88.1
unnamed: C49.1, R18.1
unnamed: ADAR1_.N10, C90.1
unnamed: ADAR2_.N5, R55.1, R78.2
unnamed: ADAR3_.N4, R56.1, R79.2
unnamed: C65.1, L10.2
unnamed: ADAR4_.N5, R58.1, R81.2
unnamed: ADAR4_.N4, R57.1, R80.2
unnamed: C54.2, R32.2, U8.1
unnamed: C54.1, R32.1, U8.4
unnamed: R22.1, U8.3
unnamed: R22.2, U8.2
unnamed: R35.1, U8.5
unnamed: IC1.4, R83.1, R146.2
unnamed: R112.2, U2.53
unnamed: D3.A, R114.1
unnamed: R113.2, U2.54
unnamed: R114.2, U2.55
unnamed: D2.A, R113.1
unnamed: C39.1, U3.19
unnamed: D4.A, R112.1
unnamed: D5.A, R110.1
unnamed: C141.1, L22.2, L26.1
unnamed: C72.1, RF_SW_3.15
unnamed: C141.2, L25.2, L27.1
unnamed: C56.2, U8.14
unnamed: R34.2, U8.16
unnamed: C51.1, U8.11
unnamed: C52.1, U8.10
unnamed: R138.2, U42.M9
unnamed: R139.2, U42.M10
unnamed: R140.2, U42.M11
unnamed: R141.2, U42.L9
unnamed: C53.2, R20.1, R21.2
unnamed: C57.2, R35.2
unnamed: C58.1, R34.1
unnamed: C63.1, C64.2, L3.1, L8.2
unnamed: R142.2, U42.E7
unnamed: R144.1, U42.H10
unnamed: R143.1, U42.K10
unnamed: R60.1, U6.6
unnamed: C184.1, U6.2, Y1.P1
unnamed: C185.1, U6.3, Y1.P3
unnamed: C186.A, C188.2, L20.1, U6.9
unnamed: C187.A, C189.1, L19.1, U6.4
unnamed: IC1.1, R145.1, U6.63
unnamed: IC1.2, R84.1, U6.62
unnamed: IC1.3, R146.1, U6.61
unnamed: C63.2, C65.2, L4.1, L8.1
unnamed: C71.1, RF_SW_3.10
unnamed: C70.1, J25.1
unnamed: C71.2, J24.1
unnamed: C126.2, RF_SW_1.3
unnamed: C129.1, RF_SW_1.15
unnamed: C128.1, RF_SW_1.10
unnamed: C126.1, J27.1
unnamed: C128.2, J26.1
unnamed: C134.2, RF_SW_2.3
unnamed: C136.1, RF_SW_2.15
unnamed: C135.1, RF_SW_2.10
unnamed: C134.1, J29.1
unnamed: C135.2, J28.1
unnamed: C142.2, RF_SW_4.3
unnamed: C144.1, RF_SW_4.15
unnamed: C143.1, RF_SW_4.10
unnamed: C142.1, J31.1
unnamed: C143.2, J30.1
unnamed: C149.2, RF_SW_7.3
unnamed: C151.1, RF_SW_7.15
unnamed: C150.1, RF_SW_7.10
unnamed: C149.1, J33.1
unnamed: C150.2, J32.1
unnamed: C163.2, RF_SW_5.3
unnamed: C166.1, RF_SW_5.15
unnamed: C165.1, RF_SW_5.10
unnamed: C163.1, J35.1
unnamed: C165.2, J34.1
unnamed: C171.2, RF_SW_6.3
unnamed: C173.1, RF_SW_6.15
unnamed: C172.1, RF_SW_6.10
unnamed: C171.1, J37.1
unnamed: C172.2, J36.1
unnamed: C197.2, RF_SW_8.3
unnamed: C199.1, RF_SW_8.15
unnamed: C198.1, RF_SW_8.10
unnamed: C197.1, J39.1
unnamed: C198.2, J38.1
unnamed: C204.2, RF_SW_10.3
unnamed: C206.1, RF_SW_10.15
unnamed: C205.1, RF_SW_10.10
unnamed: C204.1, J41.1
unnamed: C205.2, J40.1
unnamed: C211.2, RF_SW_12.3
unnamed: C213.1, RF_SW_12.15
unnamed: C212.1, RF_SW_12.10
unnamed: C211.1, J43.1
unnamed: C212.2, J42.1
unnamed: C218.2, RF_SW_11.3
unnamed: C220.1, RF_SW_11.15
unnamed: C219.1, RF_SW_11.10
unnamed: C218.1, J45.1
unnamed: C219.2, J44.1
unnamed: C225.2, RF_SW_9.3
unnamed: C227.1, RF_SW_9.15
unnamed: C226.1, RF_SW_9.10
unnamed: C225.1, J47.1
unnamed: C226.2, J46.1
unnamed: C232.2, RF_SW_14.3
unnamed: C234.1, RF_SW_14.15
unnamed: C233.1, RF_SW_14.10
unnamed: C232.1, J49.1
unnamed: C233.2, J48.1
unnamed: C239.2, RF_SW_16.3
unnamed: C241.1, RF_SW_16.15
unnamed: C240.1, RF_SW_16.10
unnamed: C239.1, J51.1
unnamed: C240.2, J50.1
unnamed: C246.2, RF_SW_15.3
unnamed: C248.1, RF_SW_15.15
unnamed: C247.1, RF_SW_15.10
unnamed: C246.1, J53.1
unnamed: C247.2, J52.1
unnamed: C253.2, RF_SW_13.3
unnamed: C255.1, RF_SW_13.15
unnamed: C254.1, RF_SW_13.10
unnamed: C253.1, J55.1
unnamed: C254.2, J54.1
unnamed: R43.2, U69.21
unnamed: OPA_4.2, R85.1, R89.1
unnamed: U11.8, X3.1
unnamed: OPA_4.6, R86.1, R90.1
unnamed: U11.1, X3.2
unnamed: R124.2, U11.5
unnamed: C261.2, R124.1, U10.1
unnamed: U73.8, X38.1
unnamed: OPA_4.9, R87.2, R91.2
unnamed: U73.1, X38.2
unnamed: R125.2, U73.5
unnamed: OPA_4.13, R88.2, R92.2
unnamed: C263.2, R125.1, U10.2
unnamed: U74.8, X39.1
unnamed: U74.1, X39.2
unnamed: R126.2, U74.5
unnamed: R41.2, U7.21
unnamed: OPA_2.2, R59.1, R95.1
unnamed: C265.2, R126.1, U10.3
unnamed: OPA_2.6, R82.1, R96.1
unnamed: U75.8, X40.1
unnamed: U75.1, X40.2
unnamed: R127.2, U75.5
unnamed: OPA_2.9, R93.2, R97.2
unnamed: C267.2, R127.1, U10.4
unnamed: U76.8, X41.1
unnamed: OPA_2.13, R94.2, R98.2
unnamed: U76.1, X41.2
unnamed: R128.2, U76.5
unnamed: C269.2, R128.1, U10.5
unnamed: U77.8, X42.1
unnamed: U77.1, X42.2
unnamed: R129.2, U77.5
unnamed: OPA_3.2, R99.1, R103.1
unnamed: C271.2, R129.1, U10.6
unnamed: OPA_3.6, R100.1, R104.1
unnamed: U78.8, X43.1
unnamed: U78.1, X43.2
unnamed: R130.2, U78.5
unnamed: OPA_3.9, R101.2, R105.2
unnamed: C273.2, R130.1, U10.7
unnamed: U79.8, X44.1
unnamed: OPA_3.13, R102.2, R106.2
unnamed: U79.1, X44.2
unnamed: R131.2, U79.5
unnamed: C275.2, R131.1, U10.8
unnamed: C277.1, U10.10
unnamed: C276.1, R132.2, U10.16
unnamed: C278.1, U10.11
unnamed: OPA_1.2, R107.1, R119.1
unnamed: U80.8, X45.1
unnamed: OPA_1.6, R108.1, R120.1
unnamed: U80.1, X45.2
unnamed: R133.2, U80.5
unnamed: C280.2, R133.1, U88.1
unnamed: OPA_1.9, R109.2, R121.2
unnamed: U81.8, X46.1
unnamed: U81.1, X46.2
unnamed: OPA_1.13, R118.2, R122.2
unnamed: R134.2, U81.5
unnamed: C282.2, R134.1, U88.2
unnamed: U82.8, X47.1
unnamed: U82.1, X47.2
unnamed: R135.2, U82.5
unnamed: C284.2, R135.1, U88.3
unnamed: U83.8, X48.1
unnamed: U83.1, X48.2
unnamed: R136.2, U83.5
unnamed: C286.2, R136.1, U88.4
unnamed: U84.8, X49.1
unnamed: U84.1, X49.2
unnamed: R137.2, U84.5
unnamed: C288.2, R137.1, U88.5
unnamed: U85.8, X50.1
unnamed: U85.1, X50.2
unnamed: R147.2, U85.5
unnamed: C290.2, R147.1, U88.6
unnamed: U86.8, X51.1
unnamed: U86.1, X51.2
unnamed: R148.2, U86.5
unnamed: C292.2, R148.1, U88.7
unnamed: U87.8, X52.1
unnamed: U87.1, X52.2
unnamed: R149.2, U87.5
unnamed: C294.2, R149.1, U88.8
unnamed: C295.1, U88.10
unnamed: C296.1, R150.2, R151.2, U88.16
unnamed: C297.1, U88.11
unnamed: R151.1, U88.13
unnamed: R153.1, U89.12
unnamed: JP5.2, U89.4
unnamed: JP6.2, U89.5
unnamed: JP19.2, U89.1
unnamed: JP12.2, U89.7
unnamed: JP14.2, U89.2
unnamed: C60.1, C61.2, L2.2, L24.1
unnamed: JP16.2, U89.8
unnamed: C299.1, U89.10
unnamed: C300.1, R152.2, R153.2, U89.16
unnamed: C301.1, U89.11
unnamed: C60.2, C62.2, L2.1, L28.1
unnamed: JP11.2, U89.6
unnamed: JP15.2, U89.3
unnamed: C268.1, L24.2
unnamed: C270.1, L28.2
PA_BIAS1_1: ADAR1_.A10, ADTR1107_3.7, C103.1
PA_BIAS1_2: ADAR2_.A10, ADTR1107_7.7, C107.1
PA_BIAS1_3: ADAR3_.A10, ADTR1107_10.7, C116.1
PA_BIAS1_4: ADAR4_.A10, ADTR1107_14.7, C120.1
PA_BIAS2_1: ADAR1_.A9, ADTR1107_1.7, C102.1
PA_BIAS2_2: ADAR2_.A9, ADTR1107_5.7, C106.1
PA_BIAS2_3: ADAR3_.A9, ADTR1107_12.7, C117.1
PA_BIAS2_4: ADAR4_.A9, ADTR1107_16.7, C121.1
PA_BIAS3_1: ADAR1_.A5, ADTR1107_2.7, C105.1
PA_BIAS3_2: ADAR2_.A5, ADTR1107_6.7, C114.1
PA_BIAS3_3: ADAR3_.A5, ADTR1107_11.7, C118.1
PA_BIAS3_4: ADAR4_.A5, ADTR1107_15.7, C122.1
PA_BIAS4_1: ADAR1_.A4, ADTR1107_4.7, C104.1
PA_BIAS4_2: ADAR2_.A4, ADTR1107_8.7, C115.1
PA_BIAS4_3: ADAR3_.A4, ADTR1107_9.7, C119.1
PA_BIAS4_4: ADAR4_.A4, ADTR1107_13.7, C123.1
RF_IO: C85.2, U16.21
RF_IO_1: ADAR1_.A7, U16.14
RF_IO_2: ADAR2_.A7, U16.10
RF_IO_3: ADAR3_.A7, U16.31
RF_IO_4: ADAR4_.A7, U16.27
RF_RX: U13.5, U$3.P$1
RF_RX_FIL: C84.2, U$3.P$2
RF_TX: U5.5, U$2.P$2
RF_TX_FIL: C83.1, U$2.P$1
RX1_1: ADAR1_.J13, ADTR1107_3.2
RX1_2: ADAR2_.J13, ADTR1107_7.2
RX1_3: ADAR3_.J13, ADTR1107_10.2
RX1_4: ADAR4_.J13, ADTR1107_14.2
RX2_1: ADAR1_.C13, ADTR1107_1.2
RX2_2: ADAR2_.C13, ADTR1107_5.2
RX2_3: ADAR3_.C13, ADTR1107_12.2
RX2_4: ADAR4_.C13, ADTR1107_16.2
RX3_1: ADAR1_.E1, ADTR1107_2.2
RX3_2: ADAR2_.E1, ADTR1107_6.2
RX3_3: ADAR3_.E1, ADTR1107_11.2
RX3_4: ADAR4_.E1, ADTR1107_15.2
RX4_1: ADAR1_.L1, ADTR1107_4.2
RX4_2: ADAR2_.L1, ADTR1107_8.2
RX4_3: ADAR3_.L1, ADTR1107_9.2
RX4_4: ADAR4_.L1, ADTR1107_13.2
STEPPER_CLK+: JP9.4, U2.119
STEPPER_CW+: JP9.2, U2.118
STM32_MISO1: U2.42, U42.G14
STM32_MISO4: JP1.8, JP13.1, U2.4
STM32_MISO_1V8: ADAR1_.M4, ADAR2_.M4, ADAR3_.M4, ADAR4_.M4, R164.2, U42.N3
STM32_MOSI1: U2.43, U42.H13
STM32_MOSI4: JP1.7, JP13.3, U2.5
STM32_MOSI_1V8: ADAR1_.M5, ADAR2_.M5, ADAR3_.M5, ADAR4_.M5, R163.2, U42.M1
STM32_NRST: C164.2, JP2.5, R111.1, S1.3, S1.4, U2.25
STM32_OSC_32_N: C18.1, U2.8, XTAL3.2
STM32_OSC_32_P: C19.1, U2.9, XTAL3.1
STM32_OSC_N: C20.1, U2.23, XTAL1.2
STM32_OSC_P: C21.1, U2.24, XTAL1.1
STM32_RX3: JP17.2, U2.70
STM32_RX5: JP8.3, U2.116
STM32_SCL1: R170.2, U2.136, U7.20, U69.20
STM32_SCL2: R172.2, U2.11, U10.14, U88.14, U89.14
STM32_SCL3: JP7.4, JP18.2, R167.2, U2.100
STM32_SCLK1: U2.41, U42.J16
STM32_SCLK4: JP1.6, JP13.2, U2.1
STM32_SCLK_1V8: ADAR1_.M6, ADAR2_.M6, ADAR3_.M6, ADAR4_.M6, R162.2, U42.P5
STM32_SDA1: R169.2, U2.137, U7.19, U69.19
STM32_SDA2: R171.2, U2.10, U10.15, U88.15, U89.15
STM32_SDA3: JP7.5, JP18.1, R168.2, U2.99
STM32_SWCLK: JP2.2, U2.109
STM32_SWDIO: JP2.4, U2.105
STM32_SWO: JP2.6, U2.133
STM32_TX3: JP17.1, U2.69
STM32_TX5: JP8.2, U2.113
STM32_USB_FS_D_N: U2.103, X53.2
STM32_USB_FS_D_P: U2.104, X53.3
STM32_USB_FS_ID: U2.102, X53.4
TR_SW_POS_1: ADAR1_.B5, ADTR1107_1.20, ADTR1107_2.20, ADTR1107_3.20, ADTR1107_4.20
TR_SW_POS_2: ADAR2_.B5, ADTR1107_5.20, ADTR1107_6.20, ADTR1107_7.20, ADTR1107_8.20
TR_SW_POS_3: ADAR3_.B5, ADTR1107_9.20, ADTR1107_10.20, ADTR1107_11.20, ADTR1107_12.20
TR_SW_POS_4: ADAR4_.B5, ADTR1107_13.20, ADTR1107_14.20, ADTR1107_15.20, ADTR1107_16.20
TX1_1: ADAR1_.L13, ADTR1107_3.5
TX1_2: ADAR2_.L13, ADTR1107_7.5
TX1_3: ADAR3_.L13, ADTR1107_10.5
TX1_4: ADAR4_.L13, ADTR1107_14.5
TX2_1: ADAR1_.E13, ADTR1107_1.5
TX2_2: ADAR2_.E13, ADTR1107_5.5
TX2_3: ADAR3_.E13, ADTR1107_12.5
TX2_4: ADAR4_.E13, ADTR1107_16.5
TX3_1: ADAR1_.C1, ADTR1107_2.5
TX3_2: ADAR2_.C1, ADTR1107_6.5
TX3_3: ADAR3_.C1, ADTR1107_11.5
TX3_4: ADAR4_.C1, ADTR1107_15.5
TX4_1: ADAR1_.J1, ADTR1107_4.5
TX4_2: ADAR2_.J1, ADTR1107_8.5
TX4_3: ADAR3_.J1, ADTR1107_9.5
TX4_4: ADAR4_.J1, ADTR1107_13.5
VG_1: OPA_2.14, R98.1, X_7.1
VG_2: OPA_4.8, R91.1, X_16.1
VG_3: OPA_2.8, R97.1, X_8.1
VG_4: OPA_4.14, R92.1, X_15.1
VG_5: OPA_2.7, R96.2, X_4.1
VG_6: OPA_4.1, R89.2, X_11.1
VG_7: OPA_2.1, R95.2, X_3.1
VG_8: OPA_4.7, R90.2, X_12.1
VG_9: OPA_1.14, R122.1, X_5.1
VG_10: OPA_3.8, R105.1, X_14.1
VG_11: OPA_1.8, R121.1, X_6.1
VG_12: OPA_3.14, R106.1, X_13.1
VG_13: OPA_1.7, R120.2, X_2.1
VG_14: OPA_3.1, R103.2, X_9.1
VG_15: OPA_1.1, R119.2, X_1.1
VG_16: OPA_3.7, R104.2, X_10.1

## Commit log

2026-03-11 Include radar system image in README
    Add image of AERIS-10 Radar System to README
2026-03-16 Fix NCO XSim test 12: widen zero-crossing range for DSP48E1 quantization
    DSP48E1 lookup table quantization causes dithering near zero crossings
    at low frequencies (1 MHz), producing ~11 sign transitions vs ~5 expected.
    Widen accepted range from [3,8] to [3,15].
2026-03-17 Phase 1 hardware bring-up prep: ILA debug probes, CDC waivers, programming scripts
    - Rename latency_buffer_2159 -> latency_buffer (module + file + all refs)
    - Add CDC waivers for 5 verified false-positive criticals to XDC
    - Add ILA debug probe insertion script (4 cores, 126 probe bits, 2 clock domains)
    - Add FPGA programming script (7-step flow with DONE pin verification)
    - Add ILA capture script (4 scenarios + health check, CSV export)
    - Add debug_ila.xdc with MARK_DEBUG fallback attributes
2026-03-19 Port validated Build 16 XDC cleanup and sync docs
2026-03-20 Add Build 24 15-point engineering report: timing, utilization, DSP/BRAM breakdown, power, DRC, methodology, congestion, routing, logic levels, build comparison, CFAR cost, verification summary
